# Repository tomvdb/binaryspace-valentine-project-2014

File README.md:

BinarySpace 2014 Valentine Project
==================================

Project we did for Valentine's day 2014

Project Details:

http://www.binaryspace.co.za/?page_id=146

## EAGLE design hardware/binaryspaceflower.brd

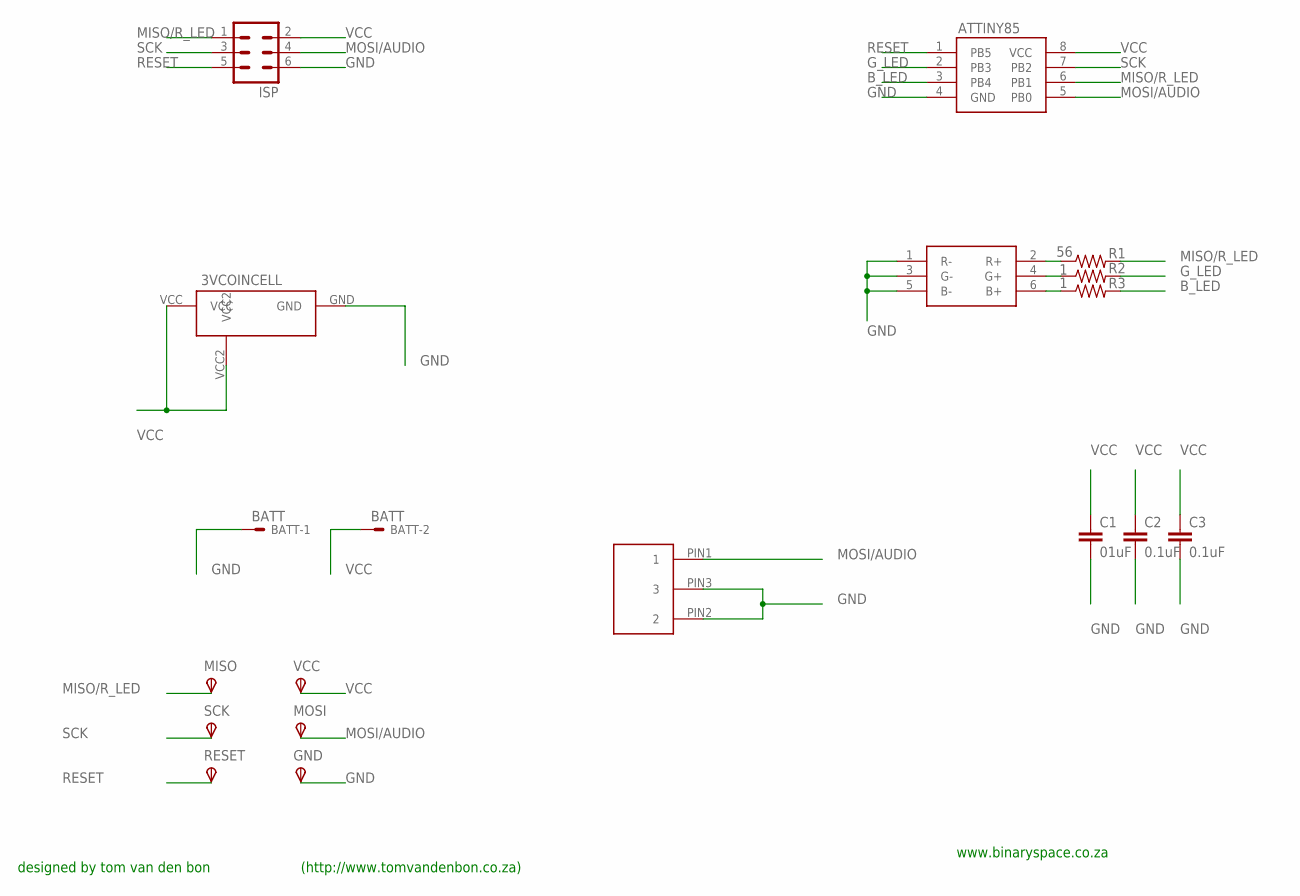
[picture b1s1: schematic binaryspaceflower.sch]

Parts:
3VCOINCELL: SMD_COINCELL_HOLDERRS; SMD_COINCELLHOLDER
ATTINY85: ATTINY85ATTINY85; SOIC-20
BATT: BATT; 332-02
C1: 01uF; C0603
C2, C3: 0.1uF; C0603
GND: TPSTP09R; TP09R
ISP: MA03-2
MISO: TPSTP09R; TP09R
MOSI: TPSTP09R; TP09R
R1: 56; R0603
R2, R3: 1; R0603
RESET: TPSTP09R; TP09R
SCK: TPSTP09R; TP09R
U$2: RGB_SMD_LEDRS; SMD_RGB_769-2996
U$3: 2.5MMAUDIOJACKMANTECH; K3624
VCC: TPSTP09R; TP09R

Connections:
B_LED: ATTINY85.3 (PB4), R3.2
GND: 3VCOINCELL.GND, ATTINY85.4 (GND), BATT.1, C1.2, C2.2, C3.2, GND.TP, ISP.6, U$2.1 (R-), U$2.3 (G-), U$2.5 (B-), U$3.PIN2 (2), U$3.PIN3 (3)
G_LED: ATTINY85.2 (PB3), R2.2
MISO/R_LED: ATTINY85.6 (PB1), ISP.1, MISO.TP, R1.2
MOSI/AUDIO: ATTINY85.5 (PB0), ISP.4, MOSI.TP, U$3.PIN1 (1)
unnamed: R1.1, U$2.2 (R+)
unnamed: R2.1, U$2.4 (G+)
unnamed: R3.1, U$2.6 (B+)
RESET: ATTINY85.1 (PB5), ISP.5, RESET.TP
SCK: ATTINY85.7 (PB2), ISP.3, SCK.TP
VCC: 3VCOINCELL.VCC, 3VCOINCELL.VCC2, ATTINY85.8 (VCC), BATT.2, C1.1, C2.1, C3.1, ISP.2, VCC.TP

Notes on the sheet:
designed by tom van den bon
(http://www.tomvandenbon.co.za)
www.binaryspace.co.za

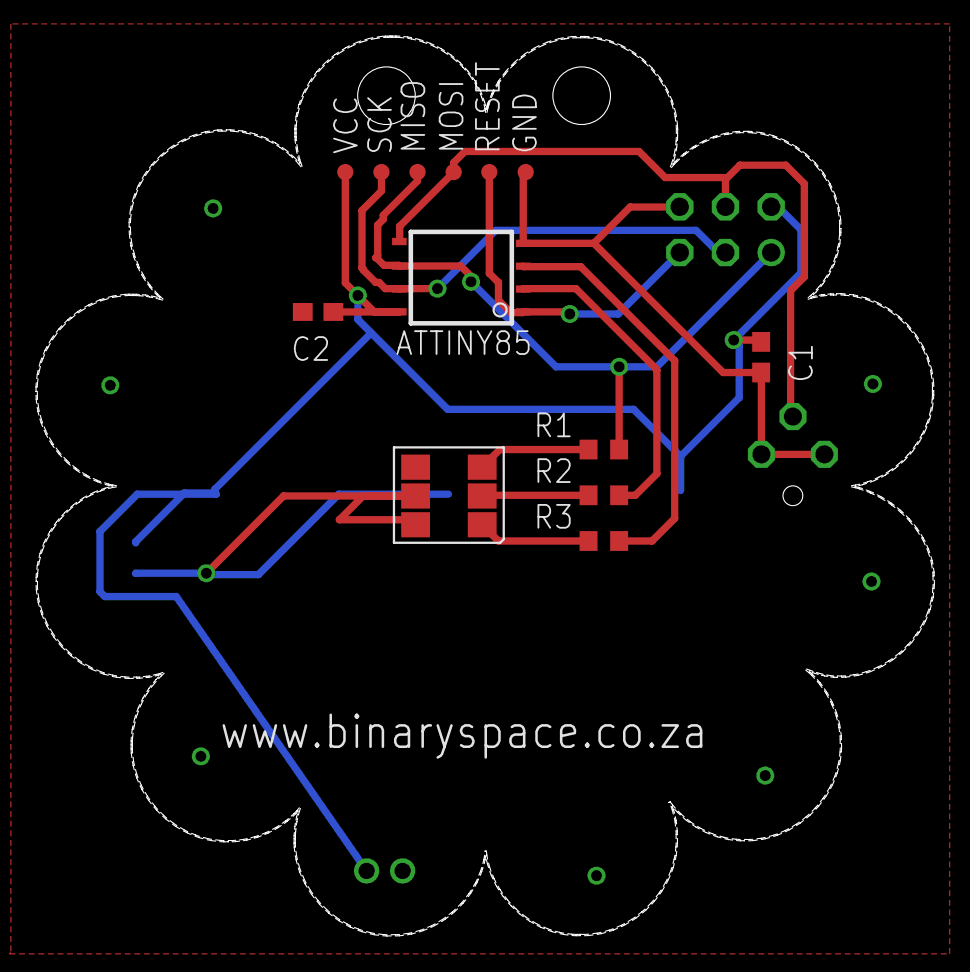
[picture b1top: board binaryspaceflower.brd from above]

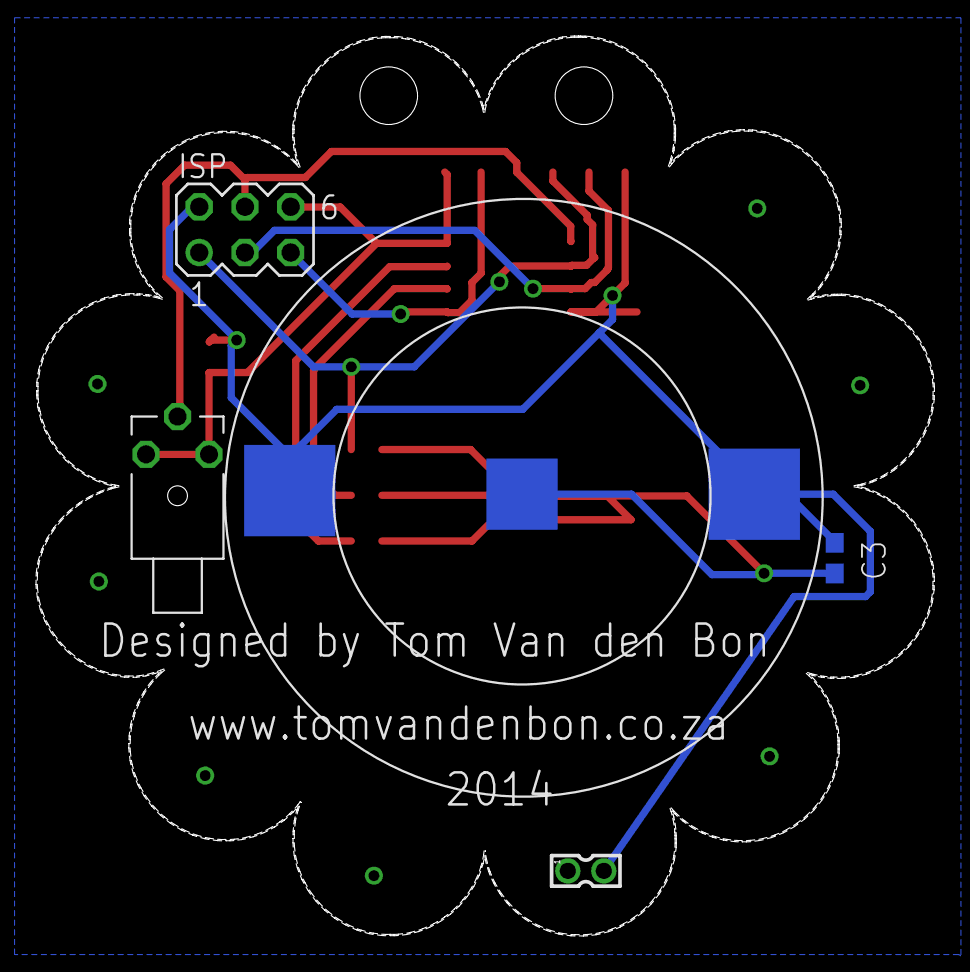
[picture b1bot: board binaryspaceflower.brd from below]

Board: 2 copper layers, 49.9 x 50.0 mm, 18 parts (4 on the bottom side), 11 nets.
